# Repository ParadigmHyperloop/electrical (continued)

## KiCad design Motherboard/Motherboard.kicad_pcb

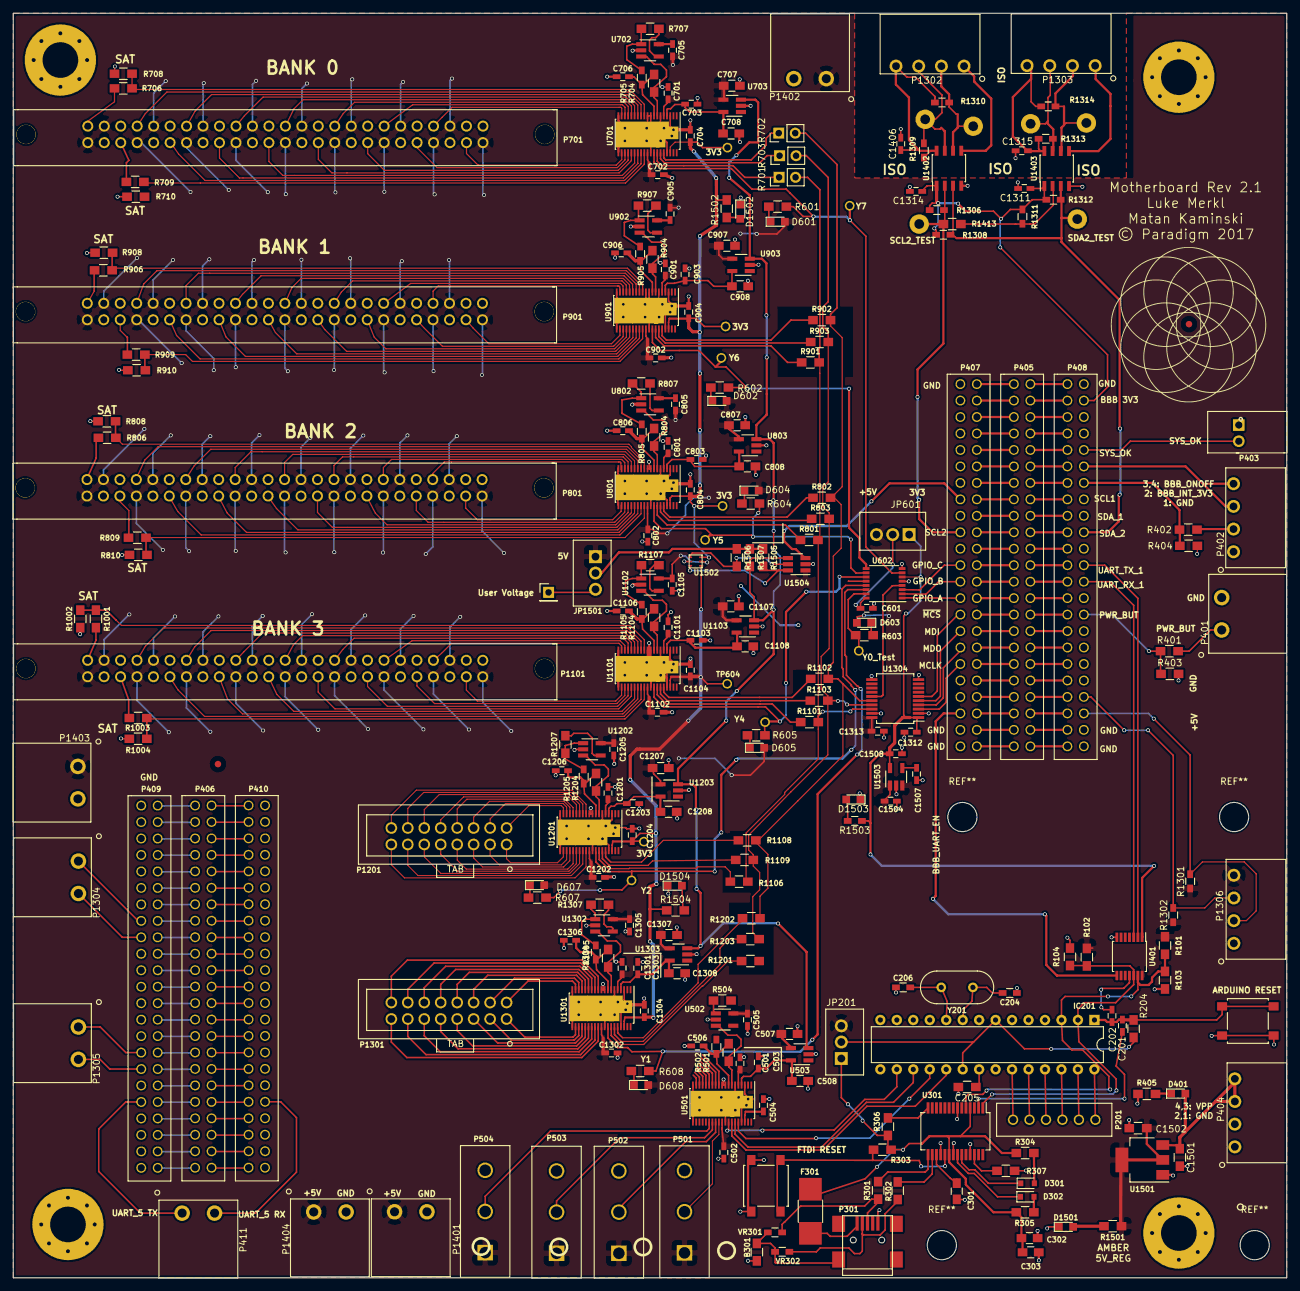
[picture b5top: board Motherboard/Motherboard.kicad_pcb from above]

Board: 2 copper layers, 196.4 x 195.1 mm, 283 parts (0 on the bottom side), 350 nets.

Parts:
B301: Ferrite__BLM21_Murata; R_0805_HandSoldering
C201, C202, C1311, C1312, C1313, C1314, C1315, C1406: 0.1uF; C_0603_HandSoldering
C204, C206: 22pF; R_0603_HandSoldering
C205: SAT; R_0805_HandSoldering
C301, C302: 100nF; C_0805_HandSoldering
C303: 4.7uF; C_0805_HandSoldering
C501, C502, C504, C505, C601, C701, C702, C704, C705, C801, C802, C804, C805, C901, C902, C904, C905, C1101, C1102, C1104, C1201, C1202, C1204, C1205, C1301, C1302, C1304, C1305, C1504: 1uF; C_0603_HandSoldering
C503, C703, C803, C903, C1103, C1105, C1203, C1303: 10uF; C_0603_HandSoldering
C506, C706, C806, C906, C1106, C1206, C1306: 150pF; C_0603_HandSoldering
C507, C508, C707, C708, C807, C808, C907, C908, C1107, C1108, C1207, C1208, C1307, C1308: 0.1uF; C_0805_HandSoldering
C1501, C1502: 10uf; R_0805_HandSoldering
C1507: 10nF; C_0603_HandSoldering
C1508: 2.2uF; C_0603_HandSoldering
D301: TX_LED; D_0805
D302: RX_LED; D_0805
D401: BLUE_LED; LED_0805
D601, D602, D603, D604, D605, D607, D608, D1502, D1503, D1504: GREEN_LED; LED_0805
D1501: AMBER_LED; LED_0805
F301: FUSE; R_1812_HandSoldering
IC201: ATMEGA328-P; DIP-28_W7.62mm
J132, J132#2, J132#3, J132#4: MOUNTING_HOLE; MountingHole_5.5mm_Pad_Via
JP201, JP601, JP1501: JUMPER3; Wafer_Vertical10x5.8x7RM2.5-3
P201: CONN_01X06; quick_6pin_2.54mm
P301: USB_OTG; USB_Mini-B
P401, P411, P1304, P1305, P1401, P1402, P1403, P1404: CONN_01X02; CONN_PHOENIX_1923869_2PIN
P402, P404, P1302, P1303: CONN_01X04; CONN_PHOENIX_1844236_4PIN
P403: CONN_01X02; pheonix_2pin_screwTerminal
P405: BeagleboneBlack_P9; header_2.54x2.54mm_spacing_pinName
P406: BeagleboneBlack_P8; header_2.54x2.54mm_spacing_pinName
P407, P408, P409, P410: CONN_02X23; header_2.54x2.54mm_spacing_pinName
P501, P502, P503, P504: CONN_01X03; 3POS_Header_TEConn_6.35mm_pitch
P701, P801, P901, P1101: CONN_02X25; 3M_50pos_latching_numbers_matchModule
P1201, P1301: CONN_02X08; OnShore_16Pin_Vert_2.54mm_spacing
P1306: CONN_01X04; CONN_PHOENIX_1844236_4PIN_1
P1406: CONN_01X01; Pin_Header_Straight_1x01_Pitch2.54mm
R101, R102, R103, R104, R706, R708, R709, R710, R806, R808, R809, R810, R906, R908, R909, R910, R1001, R1002, R1003, R1004: SAT; R_0805_HandSoldering
R204, R303, R306: 10K; R_0805_HandSoldering
R301, R302: 22; R_0805_HandSoldering
R304, R305: 270; R_0805_HandSoldering
R307, R501, R504, R704, R707, R801, R802, R803, R804, R807, R901, R902, R903, R904, R907, R1101, R1102, R1103, R1104, R1106, R1107, R1109, R1201, R1202, R1203, R1204, R1207, R1304, R1307, R1413: 0; R_0805_HandSoldering
R401, R402, R405: 10k; R_0805_HandSoldering
R403, R404: 15k; R_0805_HandSoldering
R502, R705, R805, R905, R1105, R1205, R1305: 100; R_0603_HandSoldering
R601, R602, R603, R604, R605, R607, R608: 590; R_0805_HandSoldering
R701, R702, R703: 0; Pin_Header_Straight_1x02_Pitch2.54mm
R1108: 100; R_0805_HandSoldering
R1301, R1302, R1306, R1308, R1309, R1310, R1311, R1312, R1313, R1314: 1.5k; R_0603_HandSoldering
R1501, R1502, R1504: 300; R_0805_HandSoldering
R1503: 300; R_0603_HandSoldering
R1505, R1506, R1507: 100k; R_0805_HandSoldering
SW201, SW301: SW_PUSH; SW_SPST_B3S-1000
TP601, TP602, TP603, TP604, TP607, TP611, TP612, TP613, TP614, TP616, TP618, TP1401, TP1402, TP1403, TP1404, TP1405, TP1406: TP; Measurement_Point_Round-TH_Big
U301: FT232RL; SSOP-28_5.3x10.2mm_Pitch0.65mm
U401: LEVEL_SHIFT_NXP_14TSSOP; TSSOP-14_4.4x5mm_Pitch0.65mm
U501, U701, U801, U901, U1101, U1201, U1301: ADS7953_38TSSOP; TSSOP-38_4.4x9.7mm_Pitch0.5mm
U502, U702, U802, U902, U1102, U1202, U1302: OPA192; SOT-23-5_HandSoldering
U503, U703, U803, U903, U1103, U1203, U1303: LM4132_TexasInstruments__LDO_REF; SOT-23-5_HandSoldering
U602: DEMUX_1to8_TI; TSSOP-16-1EP_4.4x5mm_Pitch0.65mm
U1304: ADuM3150_AnalogDev_7CH_ISO; SSOP-20_5.3x7.2mm_Pitch0.65mm
U1402, U1403: I2C_ISO_TI_ISO1541; SOIC-8_3.9x4.9mm_Pitch1.27mm
U1501: NCP1117ST50T3G_MountingTab; SOT-223
U1502: TPS719XX_TexasInstruments_2x2SON; TPS719XX_TexasInstruments_2x2_mm_SON
U1503: LP2985-N; SOT-23-5_HandSoldering
U1504: LM3880_TexasInstruments_PWR_SEQ; SOT-23-6_Handsoldering
VR301, VR302: 5V; R_0603_HandSoldering
Y201: 16MHz; Crystal_HC49-U_Vertical

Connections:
+3V3: C704.1, C804.1, C904.1, C1204.1, C1304.1, C1312.2, C1508.2, JP601.1, R1502.1, R1503.1, R1504.1, TP601.1, TP602.1, TP603.1, TP604.1, TP607.1, U401.1, U501.36, U602.6, U701.36, U801.36, U901.36, U1101.36, U1201.36, U1301.36, U1304.1, U1502.1, U1502.3, U1503.5
+5F: C302.1, C303.1, F301.2, JP201.1, R303.2, R304.1, R305.1, R306.2, U301.4, U301.20
+5V: C501.2, C502.1, C505.2, C507.1, C701.2, C702.1, C705.1, C707.1, C801.2, C802.1, C805.1, C807.1, C901.2, C902.1, C905.1, C907.1, C1101.2, C1102.1, C1104.1, C1107.1, C1201.2, C1202.1, C1205.2, C1207.1, C1301.2, C1302.1, C1305.2, C1307.1, C1313.1, C1502.1, C1504.2, D601.2, D602.2, D603.2, D604.2, D605.2, D607.2, D608.2, JP201.3, JP601.3, JP1501.1, P501.1, P502.1, P503.1, P504.1, P701.1, P701.4, P701.7, P701.10, P701.13, P701.16, P701.19, P701.22, P701.25, P701.28, P701.31, P701.34, P701.37, P701.40, P701.43, P701.46, P701.49, P801.1, P801.4, P801.7, P801.10, P801.13, P801.16, P801.19, P801.22, P801.25, P801.28, P801.31, P801.34, P801.37, P801.40, P801.43, P801.46, P801.49, P901.1, P901.4, P901.7, P901.10, P901.13, P901.16, P901.19, P901.22, P901.25, P901.28, P901.31, P901.34, P901.37, P901.40, P901.43, P901.46, P901.49, P1101.1, P1101.4, P1101.7, P1101.10, P1101.13, P1101.16, P1101.19, P1101.22, P1101.25, P1101.28, P1101.31, P1101.34, P1101.37, P1101.40, P1101.43, P1101.46, P1101.49, P1306.4, P1401.1, P1402.1, P1403.1, P1404.1, R101.1, R102.1, R1301.1, R1302.1, R1501.1, U401.14, U501.5, U501.29, U502.5, U503.4, U701.5, U701.29, U702.5, U703.4, U801.5, U801.29, U802.5, U803.4, U901.5, U901.29, U902.5, U903.4, U1101.5, U1101.29, U1102.5, U1103.4, U1201.5, U1201.29, U1202.5, U1203.4, U1301.5, U1301.29, U1302.5, U1303.4, U1304.20, U1501.2, U1501.4, U1502.2, U1503.1, U1503.3, U1504.1
/BBB_3V3: C1311.2, C1314.2, P408.4, R1306.1, R1308.1, R1311.1, R1312.1, U1402.1, U1403.1
/CTS: IC201.4, IC201.5
/DTR_BBB: C202.1, U401.4, U401.11
/DTR_FTDI: C201.1, U301.2
/GPIO_A: P407.27, U602.1
/GPIO_B: P407.25, U602.2
/GPIO_C: P407.23, U602.3
/MCLK: P407.35, U1304.3
/MDI: P407.31, U1304.5
/MDO: P407.33, U1304.4
/MOBO_power/3V3_EN_1: R1505.2, U1502.6, U1504.6
/MOBO_power/3V3_EN_2: R1506.2, U1502.4, U1504.5
/MOBO_power/PWR_SEQ_EN: P407.15, U1504.3
/RX_UART: IC201.3, R101.2, R103.1, U301.5, U401.13
/SCL2: P407.19, R1306.2, R1311.2, R1413.1, R1413.2, TP1405.1, U1402.2, U1403.2
/SCLK: R701.1, R801.1, R901.1, R1102.1, R1201.2, U1304.18
/SDA2: P408.20, R1308.2, R1312.2, TP1406.1, U1402.3, U1403.3
/SDI: R703.1, R803.1, R903.1, R1104.1, R1109.2, R1203.2, U1304.17
/SDO: R702.2, R802.2, R902.2, R1103.2, R1202.1, U1304.16
/SEQ_ENABLE: R1507.2, U503.3, U703.3, U803.3, U903.3, U1103.3, U1203.3, U1303.3, U1504.4
/Sheet591E8E14/Vcc: IC201.7, IC201.20, JP201.2, R204.1
/Sheet5926AD0C/CH0: P501.2, U501.28
/Sheet5926AD0C/CH1: P502.2, U501.27
/Sheet5926AD0C/CH2: P503.2, U501.26
/Sheet5926AD0C/CH3: P504.2, U501.25
/Sheet5926AD0C/MUX_DATA: C506.2, R501.1, R502.1, U501.8
/Sheet5926AD0C/MUX_OUT: R501.2, U501.7, U502.3
/Sheet5926AD0C/Vref: C503.2, C508.1, U501.4, U503.5
/Sheet5926AD0C/~CS: IC201.16, U501.31
/Sheet592695A3/BBB_INT: P402.2, R402.2
/Sheet592695A3/BBB_INT_3V3: P408.14, R402.1, R404.1
/Sheet592695A3/BBB_ONOFF: P402.3, P402.4, P408.12
/Sheet592695A3/BBB_UART_EN: P407.41, U401.8
/Sheet592695A3/CAN1_HIGH: P409.15, P1304.1
/Sheet592695A3/CAN1_LOW: P409.17, P1304.2
/Sheet592695A3/CAN2_HIGH: P409.31, P1305.1
/Sheet592695A3/CAN2_LOW: P409.33, P1305.2
/Sheet592695A3/I2C1_SCL: P408.40, P1306.3, R1302.2
/Sheet592695A3/I2C1_SDA: P408.42, P1306.2, R1301.2
/Sheet592695A3/PWR_BUT: P401.1, R401.2
/Sheet592695A3/PWR_BUT_3V3: P408.30, R401.1, R403.1
/Sheet592695A3/SYS_OK: P403.1, P408.10
/Sheet592695A3/UART1_RX_BBB: P408.26, U401.3
/Sheet592695A3/UART1_TX_BBB: P408.24, U401.2
/Sheet592695A3/UART5_RX: P410.38, P411.2
/Sheet592695A3/UART5_TX: P409.37, P411.1
/Sheet592896E3/5V_ISO_0: C1406.1, P1302.4, R1309.1, R1310.1, U1402.8
/Sheet592896E3/5V_ISO_1: C1315.1, P1303.4, R1313.1, R1314.1, U1403.8
/Sheet592896E3/GND_ISO_0: C1406.2, P1302.1, U1402.5
/Sheet592896E3/GND_ISO_1: C1315.2, P1303.1, U1403.5
/Sheet592896E3/SSR_Data_0: P1302.2, R1310.2, TP1402.1, U1402.6
/Sheet592896E3/SSR_Data_1: P1303.2, R1314.2, TP1404.1, U1403.6
/Sheet592896E3/SSR_clock_0: P1302.3, R1309.2, TP1401.1, U1402.7
/Sheet592896E3/SSR_clock_1: P1303.3, R1313.2, TP1403.1, U1403.7
/Sheet59180297/Line0/AINP: C806.2, R704.2, R805.1, U801.8
/Sheet59180297/Line0/CH0: P801.5, R809.1
/Sheet59180297/Line0/CH1: P801.11, U801.27
/Sheet59180297/Line0/CH2: P801.17, U801.26
/Sheet59180297/Line0/CH3: P801.23, U801.25
/Sheet59180297/Line0/CH4: P801.29, U801.24
/Sheet59180297/Line0/CH5: P801.35, U801.23
/Sheet59180297/Line0/CH6: P801.41, U801.22
/Sheet59180297/Line0/CH7: P801.47, U801.21
/Sheet59180297/Line0/CH8: P801.44, U801.18
/Sheet59180297/Line0/CH9: P801.38, U801.17
/Sheet59180297/Line0/CH10: P801.32, U801.16
/Sheet59180297/Line0/CH11: P801.26, U801.15
/Sheet59180297/Line0/CH12: P801.20, U801.14
/Sheet59180297/Line0/CH13: P801.14, U801.13
/Sheet59180297/Line0/CH14: P801.8, U801.12
/Sheet59180297/Line0/CH15: P801.2, R806.2
/Sheet59180297/Line0/MUX_OUT: R704.1, U801.7, U802.3
/Sheet59180297/Line0/Vref: C803.2, C808.1, U801.4, U803.5
/Sheet59180297/Line1/AINP: C706.2, R705.1, U701.8
/Sheet59180297/Line1/CH0: P701.5, R709.1
/Sheet59180297/Line1/CH1: P701.11, U701.27
/Sheet59180297/Line1/CH2: P701.17, U701.26
/Sheet59180297/Line1/CH3: P701.23, U701.25
/Sheet59180297/Line1/CH4: P701.29, U701.24
/Sheet59180297/Line1/CH5: P701.35, U701.23
/Sheet59180297/Line1/CH6: P701.41, U701.22
/Sheet59180297/Line1/CH7: P701.47, U701.21
/Sheet59180297/Line1/CH8: P701.44, U701.18
/Sheet59180297/Line1/CH9: P701.38, U701.17
/Sheet59180297/Line1/CH10: P701.32, U701.16
/Sheet59180297/Line1/CH11: P701.26, U701.15
/Sheet59180297/Line1/CH12: P701.20, U701.14
/Sheet59180297/Line1/CH13: P701.14, U701.13
/Sheet59180297/Line1/CH14: P701.8, U701.12
/Sheet59180297/Line1/CH15: P701.2, R706.2
/Sheet59180297/Line1/MUX_OUT: U701.7, U702.3
/Sheet59180297/Line1/Vref: C703.2, C708.1, U701.4, U703.5
/Sheet59180297/Line2/AINP: C906.2, R804.2, R905.1, U901.8
/Sheet59180297/Line2/CH0: P901.5, R909.1
/Sheet59180297/Line2/CH1: P901.11, U901.27
/Sheet59180297/Line2/CH2: P901.17, U901.26
/Sheet59180297/Line2/CH3: P901.23, U901.25
/Sheet59180297/Line2/CH4: P901.29, U901.24
/Sheet59180297/Line2/CH5: P901.35, U901.23
/Sheet59180297/Line2/CH6: P901.41, U901.22
/Sheet59180297/Line2/CH7: P901.47, U901.21
/Sheet59180297/Line2/CH8: P901.44, U901.18
/Sheet59180297/Line2/CH9: P901.38, U901.17
/Sheet59180297/Line2/CH10: P901.32, U901.16
/Sheet59180297/Line2/CH11: P901.26, U901.15
/Sheet59180297/Line2/CH12: P901.20, U901.14
/Sheet59180297/Line2/CH13: P901.14, U901.13
/Sheet59180297/Line2/CH14: P901.8, U901.12
/Sheet59180297/Line2/CH15: P901.2, R906.2
/Sheet59180297/Line2/MUX_OUT: R804.1, U901.7, U902.3
/Sheet59180297/Line2/Vref: C903.2, C908.1, U901.4, U903.5
/Sheet59180297/Line4/AINP: C1106.2, R904.2, R1105.1, U1101.8
/Sheet59180297/Line4/CH0: P1101.5, R1003.1
/Sheet59180297/Line4/CH1: P1101.11, U1101.27
/Sheet59180297/Line4/CH2: P1101.17, U1101.26
/Sheet59180297/Line4/CH3: P1101.23, U1101.25
/Sheet59180297/Line4/CH4: P1101.29, U1101.24
/Sheet59180297/Line4/CH5: P1101.35, U1101.23
/Sheet59180297/Line4/CH6: P1101.41, U1101.22
/Sheet59180297/Line4/CH7: P1101.47, U1101.21
/Sheet59180297/Line4/CH8: P1101.44, U1101.18
/Sheet59180297/Line4/CH9: P1101.38, U1101.17
/Sheet59180297/Line4/CH10: P1101.32, U1101.16
/Sheet59180297/Line4/CH11: P1101.26, U1101.15
/Sheet59180297/Line4/CH12: P1101.20, U1101.14
/Sheet59180297/Line4/CH13: P1101.14, U1101.13
/Sheet59180297/Line4/CH14: P1101.8, U1101.12
/Sheet59180297/Line4/CH15: P1101.2, R1001.2
/Sheet59180297/Line4/MUX_OUT: R904.1, U1101.7, U1102.3
/Sheet59180297/Line4/Vref: C1103.2, C1108.1, U1101.4, U1103.5
/Sheet59180297/Line5/AINP: C1206.2, R1204.1, R1205.1, U1201.8
/Sheet59180297/Line5/CH0: P1201.15, U1201.28
/Sheet59180297/Line5/CH1: P1201.13, U1201.27
/Sheet59180297/Line5/CH2: P1201.11, U1201.26
/Sheet59180297/Line5/CH3: P1201.9, U1201.25
/Sheet59180297/Line5/CH4: P1201.7, U1201.24
/Sheet59180297/Line5/CH5: P1201.5, U1201.23
/Sheet59180297/Line5/CH6: P1201.3, U1201.22
/Sheet59180297/Line5/CH7: P1201.1, U1201.21
/Sheet59180297/Line5/CH8: P1201.2, U1201.18
/Sheet59180297/Line5/CH9: P1201.4, U1201.17
/Sheet59180297/Line5/CH10: P1201.6, U1201.16
/Sheet59180297/Line5/CH11: P1201.8, U1201.15
/Sheet59180297/Line5/CH12: P1201.10, U1201.14
/Sheet59180297/Line5/CH13: P1201.12, U1201.13
/Sheet59180297/Line5/CH14: P1201.14, U1201.12
/Sheet59180297/Line5/CH15: P1201.16, U1201.11
/Sheet59180297/Line5/MUX_OUT: R1204.2, U1201.7, U1202.3
/Sheet59180297/Line5/Vref: C1203.2, C1208.1, U1201.4, U1203.5
/Sheet59180297/Line6/AINP: C1306.2, R1106.2, R1108.1, R1304.1, R1305.1, U1301.8
/Sheet59180297/Line6/CH0: P1301.15, U1301.28
/Sheet59180297/Line6/CH1: P1301.13, U1301.27
/Sheet59180297/Line6/CH2: P1301.11, U1301.26
/Sheet59180297/Line6/CH3: P1301.9, U1301.25
/Sheet59180297/Line6/CH4: P1301.7, U1301.24
/Sheet59180297/Line6/CH5: P1301.5, U1301.23
/Sheet59180297/Line6/CH6: P1301.3, U1301.22
/Sheet59180297/Line6/CH7: P1301.1, U1301.21
/Sheet59180297/Line6/CH8: P1301.2, U1301.18
/Sheet59180297/Line6/CH9: P1301.4, U1301.17
/Sheet59180297/Line6/CH10: P1301.6, U1301.16
/Sheet59180297/Line6/CH11: P1301.8, U1301.15
/Sheet59180297/Line6/CH12: P1301.10, U1301.14
/Sheet59180297/Line6/CH13: P1301.12, U1301.13
/Sheet59180297/Line6/CH14: P1301.14, U1301.12
/Sheet59180297/Line6/CH15: P1301.16, U1301.11
/Sheet59180297/Line6/MUX_OUT: R1106.1, R1304.2, U1301.7, U1302.3
/Sheet59180297/Line6/Vref: C1105.2, C1303.2, C1308.1, U1301.4, U1303.5
/Sheet59180297/Y0: R603.1, TP618.1, U602.15
/Sheet59180297/Y1: R608.2, U602.14, U1301.31
/Sheet59180297/Y2: R607.2, TP616.1, U602.13, U1201.31
/Sheet59180297/Y4: R605.2, TP614.1, U602.11, U1101.31
/Sheet59180297/Y5: R604.2, TP613.1, U602.10, U801.31
/Sheet59180297/Y6: R602.2, TP612.1, U602.9, U901.31
/Sheet59180297/Y7: R601.2, TP611.1, U602.7, U701.31
/TX_UART: IC201.2, R102.2, R104.1, U301.1, U401.12
/USB_FT232/PWR_EN: R306.1, U301.14
/USB_FT232/SHIELD: B301.1, P301.6, VR301.2, VR302.2
/~CS: U602.4, U1304.15
/~MCS: P407.29, U1304.6
GND: B301.2, C204.1, C205.2, C206.1, C301.2, C302.2, C303.2, C501.1, C502.2, C503.1, C504.2, C505.1, C506.1, C507.2, C508.2, C601.1, C701.1, C702.2, C703.1, C704.2, C705.2, C706.1, C707.2, C708.2, C801.1, C802.2, C803.1, C804.2, C805.2, C806.1, C807.2, C808.2, C901.1, C902.2, C903.1, C904.2, C905.2, C906.1, C907.2, C908.2, C1101.1, C1102.2, C1103.1, C1104.2, C1105.1, C1106.1, C1107.2, C1108.2, C1201.1, C1202.2, C1203.1, C1204.2, C1205.1, C1206.1, C1207.2, C1208.2, C1301.1, C1302.2, C1303.1, C1304.2, C1305.1, C1306.1, C1307.2, C1308.2, C1311.1, C1312.1, C1313.2, C1314.1, C1501.2, C1502.2, C1504.1, C1507.1, C1508.1, D1501.1, D1502.1, D1503.1, D1504.1, IC201.8, IC201.22, J132.1, J132#2.1, J132#3.1, J132#4.1, P301.5, P401.2, P402.1, P403.2, P404.1, P404.2, P407.1, P407.43, P407.45, P408.2, P408.44, P408.46, P409.1, P410.2, P501.3, P502.3, P503.3, P504.3, P701.3, P701.6, P701.9, P701.12, P701.15, P701.18, P701.21, P701.24, P701.27, P701.30, P701.33, P701.36, P701.39, P701.42, P701.45, P701.48, P701.50, P801.3, P801.6, P801.9, P801.12, P801.15, P801.18, P801.21, P801.24, P801.27, P801.30, P801.33, P801.36, P801.39, P801.42, P801.45, P801.48, P801.50, P901.3, P901.6, P901.9, P901.12, P901.15, P901.18, P901.21, P901.24, P901.27, P901.30, P901.33, P901.36, P901.39, P901.42, P901.45, P901.48, P901.50, P1101.3, P1101.6, P1101.9, P1101.12, P1101.15, P1101.18, P1101.21, P1101.24, P1101.27, P1101.30, P1101.33, P1101.36, P1101.39, P1101.42, P1101.45, P1101.48, P1101.50, P1306.1, P1401.2, P1402.2, P1403.2, P1404.2, R103.2, R104.2, R307.2, R403.2, R404.2, R405.1, R708.1, R710.1, R808.1, R810.1, R908.1, R910.1, R1002.1, R1004.1, SW201.2, SW301.1, U301.7, U301.18, U301.21, U301.25, U401.7, U501.3, U501.6, U501.9, U501.10, U501.19, U501.20, U501.30, U501.35, U502.2, U503.2, U602.5, U602.8, U701.3, U701.6, U701.9, U701.10, U701.19, U701.20, U701.30, U701.35, U702.2, U703.2, U801.3, U801.6, U801.9, U801.10, U801.19, U801.20, U801.30, U801.35, U802.2, U803.2, U901.3, U901.6, U901.9, U901.10, U901.19, U901.20, U901.30, U901.35, U902.2, U903.2, U1101.3, U1101.6, U1101.9, U1101.10, U1101.19, U1101.20, U1101.30, U1101.35, U1102.2, U1103.2, U1201.3, U1201.6, U1201.9, U1201.10, U1201.19, U1201.20, U1201.30, U1201.35, U1202.2, U1203.2, U1301.3, U1301.6, U1301.9, U1301.10, U1301.19, U1301.20, U1301.30, U1301.35, U1302.2, U1303.2, U1304.2, U1304.10, U1304.11, U1304.19, U1402.4, U1403.4, U1501.1, U1502.5, U1503.2, U1504.2
unnamed: C201.2, C202.2, IC201.1, R204.2, SW201.1
unnamed: C204.2, IC201.9, Y201.1
unnamed: C205.1, IC201.21
unnamed: C206.2, IC201.10, Y201.2
unnamed: C301.1, U301.17
unnamed: C601.2, JP601.2, U602.16
unnamed: C1507.2, U1503.4
unnamed: D301.1, U301.23
unnamed: D301.2, R304.2
unnamed: D302.1, U301.22
unnamed: D302.2, R305.2
unnamed: D401.1, R405.2
unnamed: D601.1, R601.1
unnamed: D602.1, R602.1
unnamed: D603.1, R603.2
unnamed: D604.1, R604.1
unnamed: D605.1, R605.1
unnamed: D607.1, R607.1
unnamed: D608.1, R608.1
unnamed: D1501.2, R1501.2
unnamed: D1502.2, R1502.2
unnamed: D1503.2, R1503.2
unnamed: D1504.2, R1504.2
unnamed: F301.1, P301.1
unnamed: IC201.23, P201.1
unnamed: IC201.24, P201.2
unnamed: IC201.25, P201.3
unnamed: IC201.26, P201.4
unnamed: IC201.27, P201.5
unnamed: IC201.28, P201.6
unnamed: JP1501.2, R1505.1, R1506.1, R1507.1
unnamed: JP1501.3, P1406.1
unnamed: P301.2, R302.2, VR302.1
unnamed: P301.3, R301.2, VR301.1
unnamed: P405.1, P407.2
unnamed: P405.2, P408.1
unnamed: P405.3, P407.4
unnamed: P405.4, P408.3
unnamed: P405.5, P407.6
unnamed: P405.6, P408.5
unnamed: P405.7, P407.8
unnamed: P405.8, P408.7
unnamed: P405.9, P407.10
unnamed: P405.10, P408.9
unnamed: P405.11, P407.12
unnamed: P405.12, P408.11
unnamed: P405.13, P407.14
unnamed: P405.14, P408.13
unnamed: P405.15, P407.16
unnamed: P405.16, P408.15
unnamed: P405.17, P407.18
unnamed: P405.18, P408.17
unnamed: P405.19, P407.20
unnamed: P405.20, P408.19
unnamed: P405.21, P407.22
unnamed: P405.22, P408.21
unnamed: P405.23, P407.24
unnamed: P405.24, P408.23
unnamed: P405.25, P407.26
unnamed: P405.26, P408.25
unnamed: P405.27, P407.28
unnamed: P405.28, P408.27
unnamed: P405.29, P407.30
unnamed: P405.30, P408.29
unnamed: P405.31, P407.32
unnamed: P405.32, P408.31
unnamed: P405.33, P407.34
unnamed: P405.34, P408.33
unnamed: P405.35, P407.36
unnamed: P405.36, P408.35
unnamed: P405.37, P407.38
unnamed: P405.38, P408.37
unnamed: P405.39, P407.40
unnamed: P405.40, P408.39
unnamed: P405.41, P407.42
unnamed: P405.42, P408.41
unnamed: P405.43, P407.44
unnamed: P405.44, P408.43
unnamed: P405.45, P407.46
unnamed: P405.46, P408.45
unnamed: P406.1, P409.2
unnamed: P406.2, P410.1
unnamed: P406.3, P409.4
unnamed: P406.4, P410.3
unnamed: P406.5, P409.6
unnamed: P406.6, P410.5
unnamed: P406.7, P409.8
unnamed: P406.8, P410.7
unnamed: P406.9, P409.10
unnamed: P406.10, P410.9
unnamed: P406.11, P409.12
unnamed: P406.12, P410.11
unnamed: P406.13, P409.14
unnamed: P406.14, P410.13
unnamed: P406.15, P409.16
unnamed: P406.16, P410.15
unnamed: P406.17, P409.18
unnamed: P406.18, P410.17
unnamed: P406.19, P409.20
unnamed: P406.20, P410.19
unnamed: P406.21, P409.22
unnamed: P406.22, P410.21
unnamed: P406.23, P409.24
unnamed: P406.24, P410.23
unnamed: P406.25, P409.26
unnamed: P406.26, P410.25
unnamed: P406.27, P409.28
unnamed: P406.28, P410.27
unnamed: P406.29, P409.30
unnamed: P406.30, P410.29
unnamed: P406.31, P409.32
unnamed: P406.32, P410.31
unnamed: P406.33, P409.34
unnamed: P406.34, P410.33
unnamed: P406.35, P409.36
unnamed: P406.36, P410.35
unnamed: P406.37, P409.38
unnamed: P406.38, P410.37
unnamed: P406.39, P409.40
unnamed: P406.40, P410.39
unnamed: P406.41, P409.42
unnamed: P406.42, P410.41
unnamed: P406.43, P409.44
unnamed: P406.44, P410.43
unnamed: P406.45, P409.46
unnamed: P406.46, P410.45
unnamed: R301.1, U301.15
unnamed: R302.1, U301.16
unnamed: R303.1, SW301.2, U301.19
unnamed: R307.1, U301.26
unnamed: R502.2, R504.1, U502.1
unnamed: R504.2, U502.4
unnamed: R701.2, U801.32
unnamed: R702.1, U801.34
unnamed: R703.2, U801.33
unnamed: R705.2, R707.1, U702.1
unnamed: R706.1, R708.2, U701.11
unnamed: R707.2, U702.4
unnamed: R709.2, R710.2, U701.28
unnamed: R801.2, U901.32
unnamed: R802.1, U901.34
unnamed: R803.2, U901.33
unnamed: R805.2, R807.1, U802.1
unnamed: R806.1, R808.2, U801.11
unnamed: R807.2, U802.4
unnamed: R809.2, R810.2, U801.28
unnamed: R901.2, U1101.32
unnamed: R902.1, U1101.34
unnamed: R903.2, U1101.33
unnamed: R905.2, R907.1, U902.1
unnamed: R906.1, R908.2, U901.11
unnamed: R907.2, U902.4
unnamed: R909.2, R910.2, U901.28
unnamed: R1001.1, R1002.2, U1101.11
unnamed: R1003.2, R1004.2, U1101.28
unnamed: R1101.1, R1108.2
unnamed: R1102.2, U1301.32
unnamed: R1103.1, U1301.34
unnamed: R1104.2, U1301.33
unnamed: R1105.2, R1107.1, U1102.1
unnamed: R1107.2, U1102.4
unnamed: R1205.2, R1207.1, U1202.1
unnamed: R1207.2, U1202.4
unnamed: R1305.2, R1307.1, U1302.1
unnamed: R1307.2, U1302.4
VPP: C1501.1, D401.2, P404.3, P404.4, U1501.3

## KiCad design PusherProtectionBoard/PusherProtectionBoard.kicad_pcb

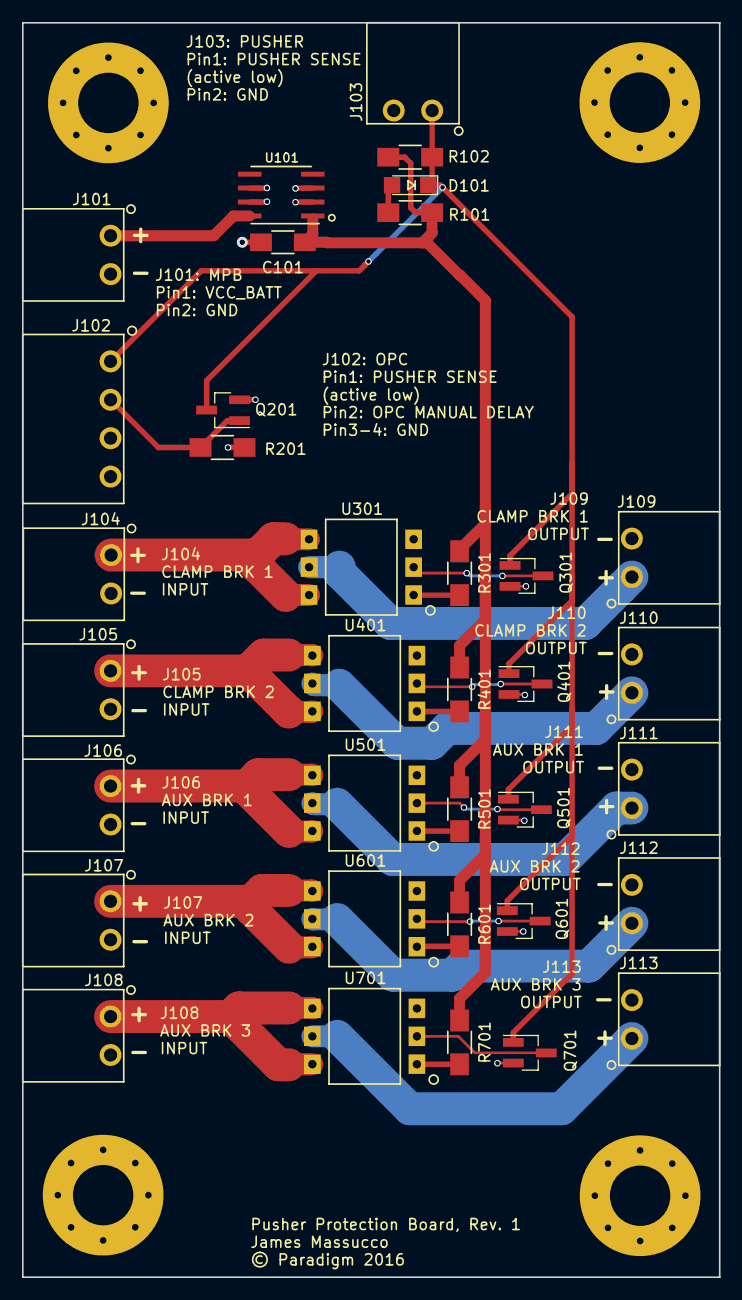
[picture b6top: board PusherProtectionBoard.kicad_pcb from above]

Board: 2 copper layers, 63.5 x 114.3 mm, 39 parts (0 on the bottom side), 26 nets.

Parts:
C101: 10uF; C_1206_HandSoldering
D101: RED; LED_1206
J101, J103, J104, J105, J106, J107, J108, J109, J110, J111, J112, J113: CONN_01X02; CONN_PHOENIX_1844210_2PIN
J102: CONN_01X04; CONN_PHOENIX_1844236_4PIN_1
J114, J115, J116, J117: MOUNTING_HOLE; MountingHole_5.5mm_Pad_Via
Q201, Q301, Q401, Q501, Q601, Q701: NFET; SOT-23_Handsoldering
R101, R301, R401, R501, R601, R701: 910; R_1206_HandSoldering
R102: 2k; R_1206_HandSoldering
R201: 1M; R_1206_HandSoldering
U101: LM2936HV; LM2936HV_SOIC8
U301, U401, U501, U601, U701: SSR; VISHAY_6SMD_OPTOCOUPLER

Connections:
5V0: C101.1, R101.1, R102.2, R301.1, R401.1, R501.1, R601.1, R701.1, U101.1
/Brake Interlock - Aux Brake 1/24V_SUPPLY: J106.1, U501.4, U501.6
/Brake Interlock - Aux Brake 1/PUSHER: D101.1, J102.1, J103.1, Q201.3, Q301.1, Q401.1, Q501.1, Q601.1, Q701.1, R102.1
/Brake Interlock - Aux Brake 1/TO_BRAKE: J111.1, U501.5
/Brake Interlock - Aux Brake 2/24V_SUPPLY: J107.1, U601.4, U601.6
/Brake Interlock - Aux Brake 2/TO_BRAKE: J112.1, U601.5
/Brake Interlock - Aux Brake 3/24V_SUPPLY: J108.1, U701.4, U701.6
/Brake Interlock - Aux Brake 3/TO_BRAKE: J113.1, U701.5
/Brake Interlock - Clamp Brake 1/24V_SUPPLY: J104.1, U301.4, U301.6
/Brake Interlock - Clamp Brake 1/TO_BRAKE: J109.1, U301.5
/Brake Interlock - Clamp Brake 2/24V_SUPPLY: J105.1, U401.4, U401.6
/Brake Interlock - Clamp Brake 2/TO_BRAKE: J110.1, U401.5
/Pusher Delay/OPC_PUSHER_REL_DELAY: J102.2, Q201.1, R201.1
GND: C101.2, J101.2, J102.3, J102.4, J103.2, J104.2, J105.2, J106.2, J107.2, J108.2, J109.2, J110.2, J111.2, J112.2, J113.2, J114.1, J115.1, J116.1, J117.1, Q201.2, Q301.2, Q401.2, Q501.2, Q601.2, Q701.2, R201.2, U101.2
unnamed: D101.2, R101.2
unnamed: J101.1, U101.8
unnamed: Q301.3, U301.2
unnamed: Q401.3, U401.2
unnamed: Q501.3, U501.2
unnamed: Q601.3, U601.2
unnamed: Q701.3, U701.2
unnamed: R301.2, U301.1
unnamed: R401.2, U401.1
unnamed: R501.2, U501.1
unnamed: R601.2, U601.1
unnamed: R701.2, U701.1

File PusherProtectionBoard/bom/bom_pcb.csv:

Item,Reference(s),References (trunc),Value,Quantity,Quantity (x1.5),DigiKey PN,Mfg.,Mfg. PN
1,C101,C101,10uF,1,2,311-2007-1-ND,Yageo,CC1206ZRY5V6BB106
2,D101,D101,RED,1,2,754-1940-1-ND,Kingbright,APT3216LSECK/J3-PRV
3,J101 J103 J104 J105 J106 J107 J108 J109 J110 J111 J112 J113,J101 J103 J104 ,CONN_01X02,12,18,277-2416-ND,Phoenix,1844210
4,J102,J102,CONN_01X04,1,2,277-2419-ND,Phoenix,1844236
5,J114 J115 J116 J117,J114 J115 J116 ,MOUNTING_HOLE,4,6,,,
6,Q201 Q301 Q401 Q501 Q601 Q701,Q201 Q301 Q401 ,NFET,6,9,BSS123NCT-ND,Fairchild,BSS123
7,R101 R301 R401 R501 R601 R701,R101 R301 R401 ,910,6,9,311-910FRCT-ND,Yageo,RC1206FR-07910RL
8,R102,R102,10k,1,2,311-10.0KFRCT-ND,Yageo,RC1206FR-0710KL
9,R201,R201,1M,1,2,311-1.0MERCT-ND,Yageo,RC1206JR-071ML
10,U101,U101,LM2936HV,1,2,LM2936HVMAX-5.0/NOPBCT-ND,Texas Instruments,LM2936HVMAX-5.0/NOPB
11,U301 U401 U501 U601 U701,U301 U401 U501 ,SSR,5,8,VO14642AABCT-ND,Vishay,VO14642AABTR

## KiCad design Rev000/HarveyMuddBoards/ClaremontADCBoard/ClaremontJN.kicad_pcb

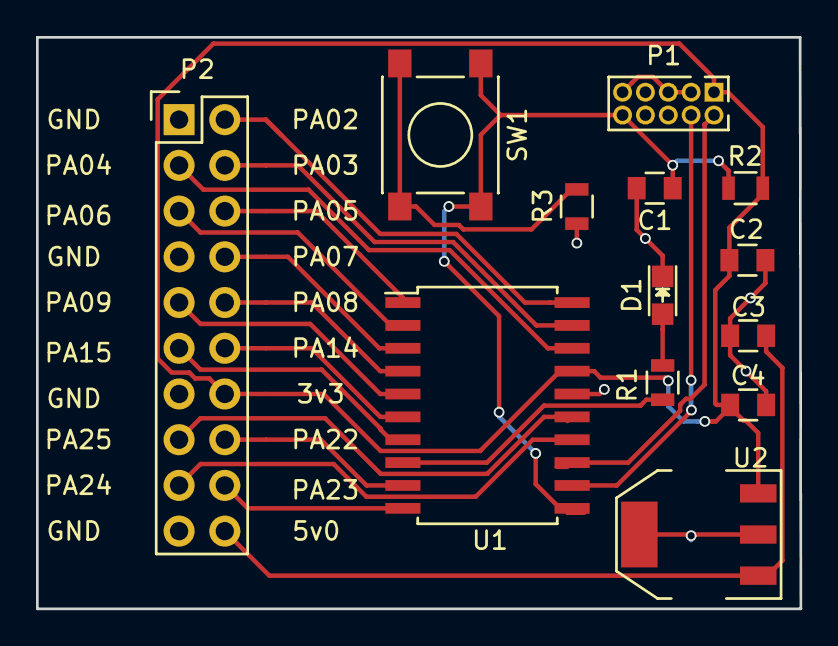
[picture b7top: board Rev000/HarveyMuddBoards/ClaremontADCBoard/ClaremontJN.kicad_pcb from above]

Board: 2 copper layers, 42.4 x 31.8 mm, 13 parts (0 on the bottom side), 23 nets.

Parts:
C1: .1μF; C_0805
C2: 0.1µF; C_0805
C3, C4: 10µF; C_0805
D1: ULED1; LED_0805
P1: JTAG; Pin_Header_Straight_2x05_Pitch1.27mm
P2: CONN_02X10; Pin_Header_Straight_2x10
R1, R3: 330R; R_0805
R2: 4.7kR; R_0805
SW1: Reset; SW_SPST_PTS645
U1: uC_ATSAMD11D14A-SS; SOIC-20_7.5x12.8mm_Pitch1.27mm
U2: LDO-TL1963-SOT223; SOT-223

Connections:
/3v3: C2.2, C4.1, P1.1, P2.14, R2.1, U1.17, U2.3
/5v0: C3.1, P2.20, U2.1
/PA02-AIN0: P2.2, U1.20
/PA03-AIN1: P2.4, U1.19
/PA04-AIN2: P2.3, U1.18
/PA05-AIN3: P2.6, U1.1
/PA06-AIN4: P2.5, U1.2
/PA07-AIN5: P2.8, U1.3
/PA08-TX: P2.10, U1.4
/PA09-RX: P2.9, U1.5
/PA14-AIN6: P2.12, U1.6
/PA15-AIN7: P2.11, U1.7
/PA16-ULED1: R1.2, U1.8
/PA22-SDA: P2.16, U1.9
/PA23-SCL: P2.18, U1.10
/PA24: P2.17, U1.14
/PA25: P2.15, U1.15
/SWCLK: P1.4, U1.12
/SWDIO: P1.2, U1.13
/nReset: C1.1, P1.10, R2.2, SW1.1, U1.11
GND: C1.2, C2.1, C3.2, C4.2, D1.1, P1.3, P1.5, P1.9, P2.1, P2.7, P2.13, P2.19, R3.2, U1.16, U2.2, U2.4
unnamed: D1.2, R1.1
unnamed: R3.1, SW1.2

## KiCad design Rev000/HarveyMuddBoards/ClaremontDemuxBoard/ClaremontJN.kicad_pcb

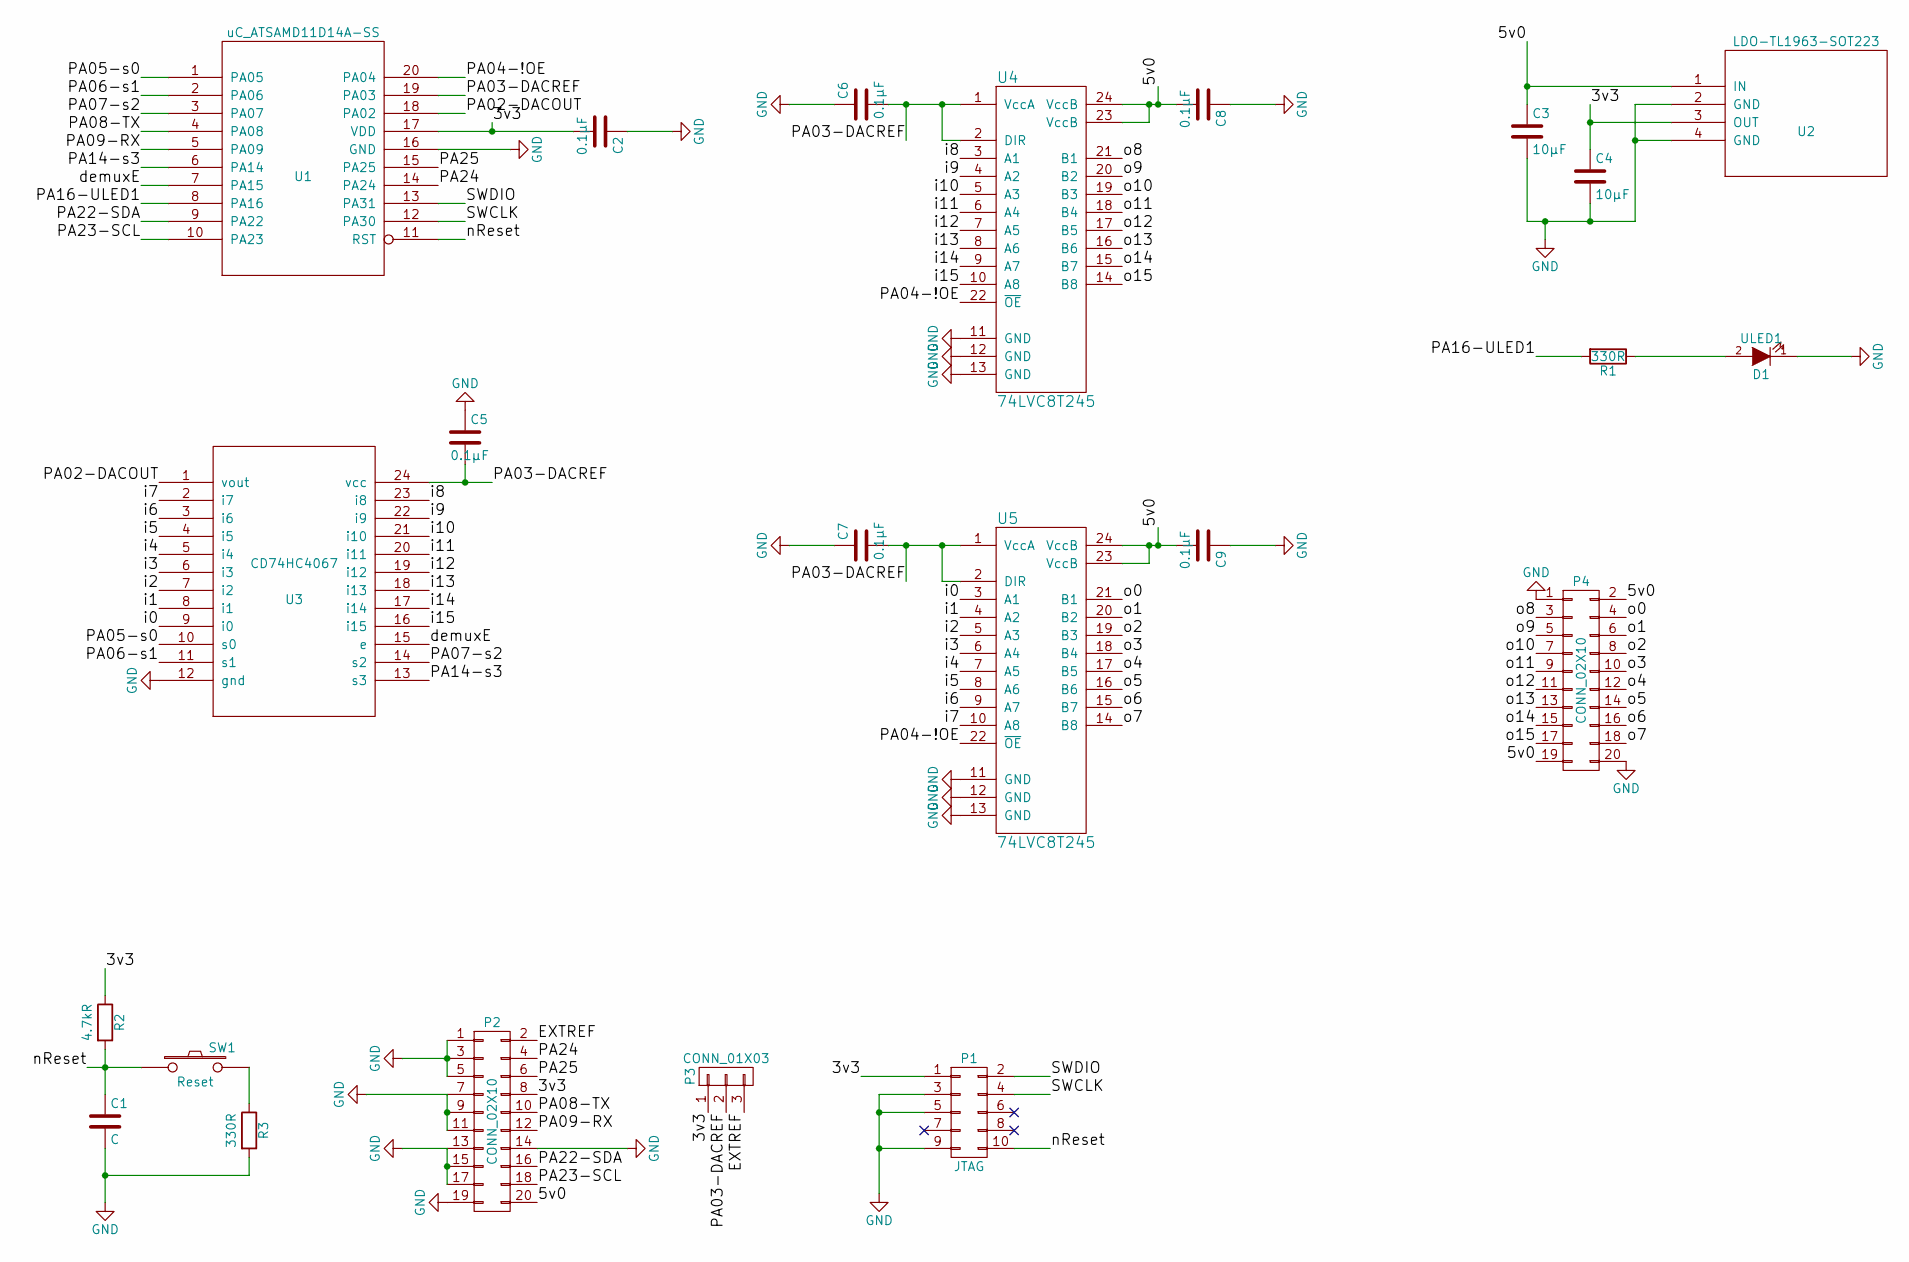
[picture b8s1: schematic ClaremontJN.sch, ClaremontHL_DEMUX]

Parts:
C1: C; C_0805
C2, C5, C6, C7, C8, C9: 0.1µF; C_0805
C3, C4: 10µF; C_0805
D1: ULED1; LED_0805
P1: JTAG; Pin_Header_Straight_2x05_Pitch1.27mm
P2, P4: CONN_02X10; Pin_Header_Straight_2x10
P3: CONN_01X03; Pin_Header_Straight_1x03
R1, R3: 330R; R_0805
R2: 4.7kR; R_0805
SW1: Reset; SW_SPST_PTS645
U1: uC_ATSAMD11D14A-SS; SOIC-20_7.5x12.8mm_Pitch1.27mm
U2: LDO-TL1963-SOT223; SOT-223
U3: CD74HC4067; DEMUX
U4, U5: 74LVC8T245; Translator

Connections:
/3v3: C2.2, C4.1, P1.1, P2.8, P3.1, R2.1, U1.17 (VDD), U2.3 (OUT)
/5v0: C3.1, C8.2, C9.2, P2.20, P4.2, P4.19, U2.1 (IN), U4.23 (VccB), U4.24 (VccB), U5.23 (VccB), U5.24 (VccB)
/EXTREF: P2.2, P3.3
/PA02-DACOUT: U1.18 (PA02), U3.1 (vout)
/PA03-DACREF: C5.2, C6.2, C7.2, P3.2, U1.19 (PA03), U3.24 (vcc), U4.1 (VccA), U4.2 (DIR), U5.1 (VccA), U5.2 (DIR)
/PA04-!OE: U1.20 (PA04), U4.22 (~OE), U5.22 (~OE)
/PA05-s0: U1.1 (PA05), U3.10 (s0)
/PA06-s1: U1.2 (PA06), U3.11 (s1)
/PA07-s2: U1.3 (PA07), U3.14 (s2)
/PA08-TX: P2.10, U1.4 (PA08)
/PA09-RX: P2.12, U1.5 (PA09)
/PA14-s3: U1.6 (PA14), U3.13 (s3)
/PA16-ULED1: R1.2, U1.8 (PA16)
/PA22-SDA: P2.16, U1.9 (PA22)
/PA23-SCL: P2.18, U1.10 (PA23)
/PA24: P2.4, U1.14 (PA24)
/PA25: P2.6, U1.15 (PA25)
/SWCLK: P1.4, U1.12 (PA30)
/SWDIO: P1.2, U1.13 (PA31)
/demuxE: U1.7 (PA15), U3.15 (e)
/i0: U3.9 (i0), U5.3 (A1)
/i1: U3.8 (i1), U5.4 (A2)
/i2: U3.7 (i2), U5.5 (A3)
/i3: U3.6 (i3), U5.6 (A4)
/i4: U3.5 (i4), U5.7 (A5)
/i5: U3.4 (i5), U5.8 (A6)
/i6: U3.3 (i6), U5.9 (A7)
/i7: U3.2 (i7), U5.10 (A8)
/i8: U3.23 (i8), U4.3 (A1)
/i9: U3.22 (i9), U4.4 (A2)
/i10: U3.21 (i10), U4.5 (A3)
/i11: U3.20 (i11), U4.6 (A4)
/i12: U3.19 (i12), U4.7 (A5)
/i13: U3.18 (i13), U4.8 (A6)
/i14: U3.17 (i14), U4.9 (A7)
/i15: U3.16 (i15), U4.10 (A8)
/nReset: C1.1, P1.10, R2.2, SW1.1, U1.11 (RST)
/o0: P4.4, U5.21 (B1)
/o1: P4.6, U5.20 (B2)
/o2: P4.8, U5.19 (B3)
/o3: P4.10, U5.18 (B4)
/o4: P4.12, U5.17 (B5)
/o5: P4.14, U5.16 (B6)
/o6: P4.16, U5.15 (B7)
/o7: P4.18, U5.14 (B8)
/o8: P4.3, U4.21 (B1)
/o9: P4.5, U4.20 (B2)
/o10: P4.7, U4.19 (B3)
/o11: P4.9, U4.18 (B4)
/o12: P4.11, U4.17 (B5)
/o13: P4.13, U4.16 (B6)
/o14: P4.15, U4.15 (B7)
/o15: P4.17, U4.14 (B8)
GND: C1.2, C2.1, C3.2, C4.2, C5.1, C6.1, C7.1, C8.1, C9.1, D1.1 (K), P1.3, P1.5, P1.9, P2.1, P2.3, P2.5, P2.7, P2.9, P2.11, P2.13, P2.14, P2.15, P2.17, P2.19, P4.1, P4.20, R3.2, U1.16 (GND), U2.2 (GND), U2.4 (GND), U3.12 (gnd), U4.11 (GND), U4.12 (GND), U4.13 (GND), U5.11 (GND), U5.12 (GND), U5.13 (GND)
unnamed: D1.2 (A), R1.1
unnamed: R3.1, SW1.2

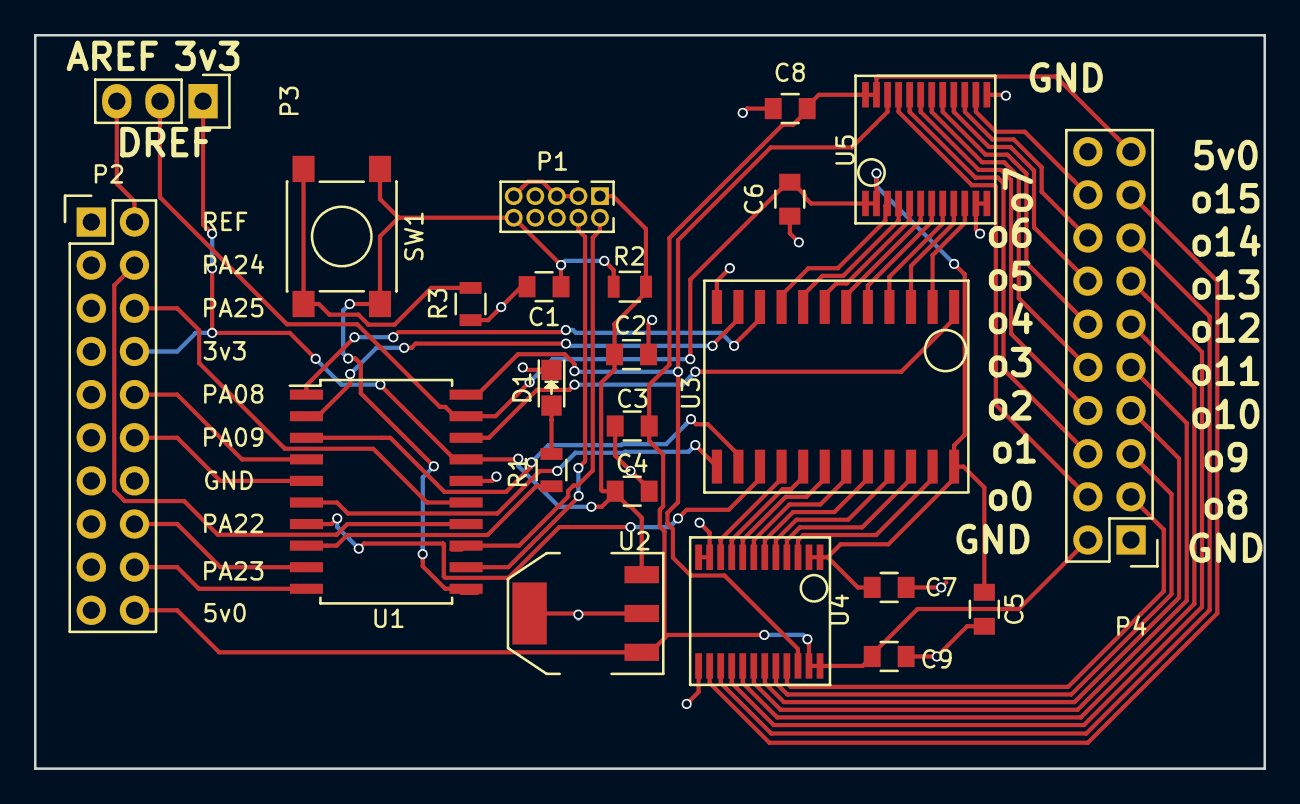
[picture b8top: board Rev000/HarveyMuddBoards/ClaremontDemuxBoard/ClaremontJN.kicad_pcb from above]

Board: 2 copper layers, 72.4 x 43.2 mm, 23 parts (0 on the bottom side), 56 nets.
